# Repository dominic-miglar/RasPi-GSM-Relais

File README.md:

# RasPi-GSM-Relais

## Folder structure

#### data_sheets

contains the data sheets of the components

#### eagle

contains the eagle files

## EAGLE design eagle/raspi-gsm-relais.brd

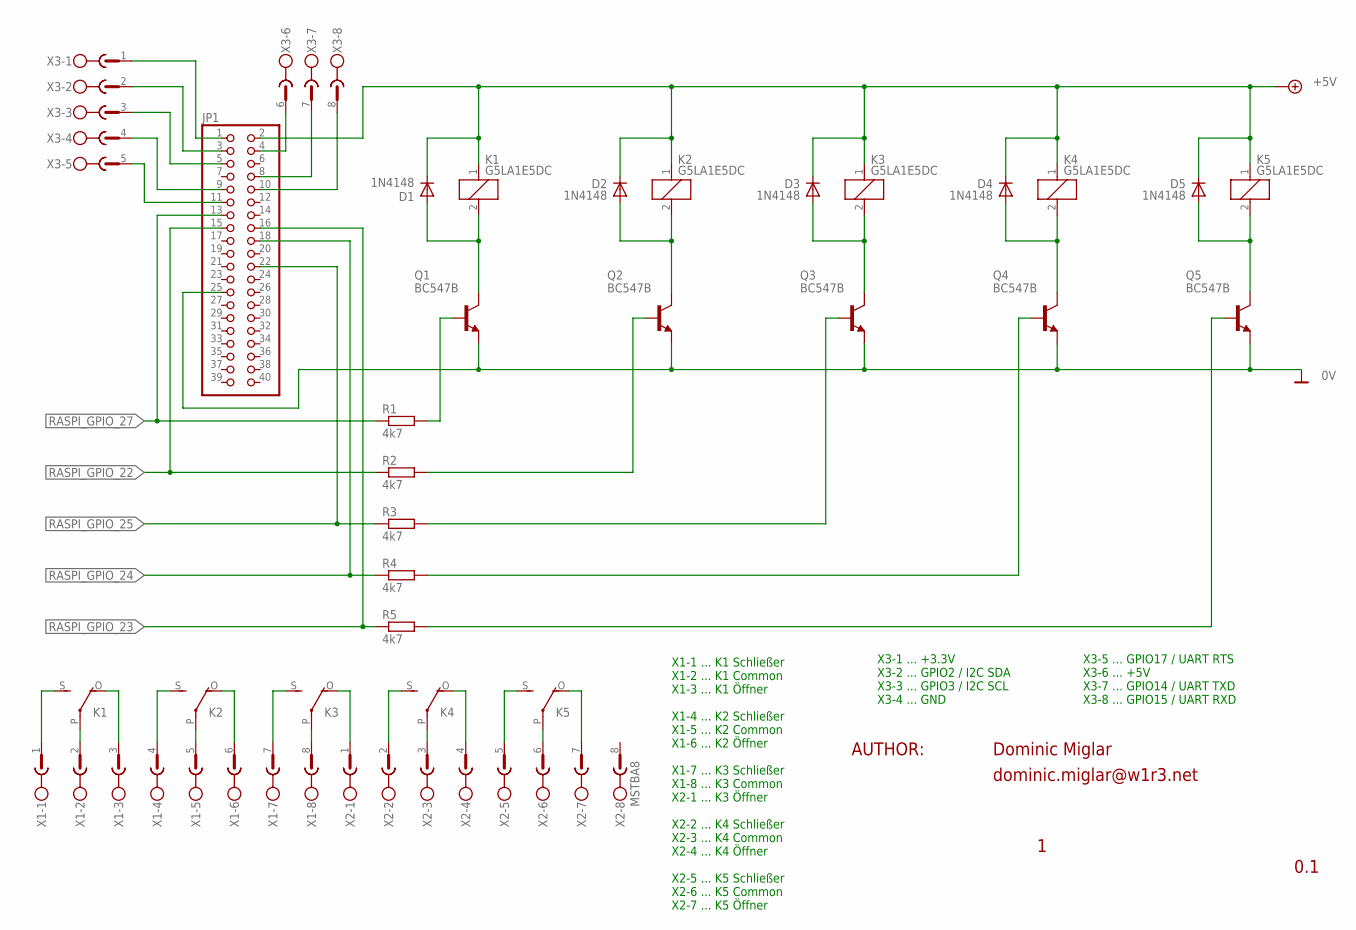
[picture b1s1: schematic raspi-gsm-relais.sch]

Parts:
D1, D2, D3, D4, D5: 1N4148; DO35-10
JP1: PINHD-2X20; 2X20
K1, K2, K3, K4, K5: G5LA1E5DC; G5LE
Q1, Q2, Q3, Q4, Q5: BC547B; TO92
R1, R2, R3, R4, R5: 4k7; 0207/10
X1, X2, X3: MSTBA8

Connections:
0V: JP1.25, Q1.1 (E), Q2.1 (E), Q3.1 (E), Q4.1 (E), Q5.1 (E)
+5V: D1.C, D2.C, D3.C, D4.C, D5.C, JP1.2, K1.1, K2.1, K3.1, K4.1, K5.1
unnamed: D1.A, K1.2, Q1.3 (C)
unnamed: D2.A, K2.2, Q2.3 (C)
unnamed: D3.A, K3.2, Q3.3 (C)
unnamed: D4.A, K4.2, Q4.3 (C)
unnamed: D5.A, K5.2, Q5.3 (C)
unnamed: JP1.1, X3.1
unnamed: Q2.2 (B), R2.2
unnamed: Q3.2 (B), R3.2
unnamed: Q4.2 (B), R4.2
unnamed: Q5.2 (B), R5.2
unnamed: K4.P, X2.3
unnamed: K1.P, X1.2
unnamed: K1.O, X1.3
unnamed: K1.S, X1.1
unnamed: K2.P, X1.5
unnamed: K2.O, X1.6
unnamed: K2.S, X1.4
unnamed: K3.P, X1.8
unnamed: K3.O, X2.1
unnamed: K3.S, X1.7
unnamed: K4.O, X2.4
unnamed: K4.S, X2.2
unnamed: K5.P, X2.6
unnamed: K5.S, X2.5
unnamed: K5.O, X2.7
unnamed: Q1.2 (B), R1.2
unnamed: JP1.3, X3.2
unnamed: JP1.5, X3.3
unnamed: JP1.9, X3.4
unnamed: JP1.11, X3.5
unnamed: JP1.4, X3.6
unnamed: JP1.8, X3.7
unnamed: JP1.10, X3.8
RASPI_GPIO_22: JP1.15, R2.1
RASPI_GPIO_23: JP1.16, R5.1
RASPI_GPIO_24: JP1.18, R4.1
RASPI_GPIO_25: JP1.22, R3.1
RASPI_GPIO_27: JP1.13, R1.1

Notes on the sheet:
X1-1 ... K1 Schließer X1-2 ... K1 Common X1-3 ... K1 Öffner X1-4 ... K2 Schließer X1-5 ... K2 Common X1-6 ... K2 Öffner X1-7 ... K3 Schließer X1-8 ... K3 Common X2-1 ... K3 Öffner X2-2 ... K4 Schließer X2-3 ... K4 Common X2-4 ... K4 Öffner X2-5 ... K5 Schließer X2-6 ... K5 Common X2-7 ... K5 Öffner
X3-1 ... +3.3V X3-2 ... GPIO2 / I2C SDA X3-3 ... GPIO3 / I2C SCL X3-4 ... GND
X3-5 ... GPIO17 / UART RTS X3-6 ... +5V X3-7 ... GPIO14 / UART TXD X3-8 ... GPIO15 / UART RXD
AUTHOR:
dominic.miglar@w1r3.net
Dominic Miglar
0.1

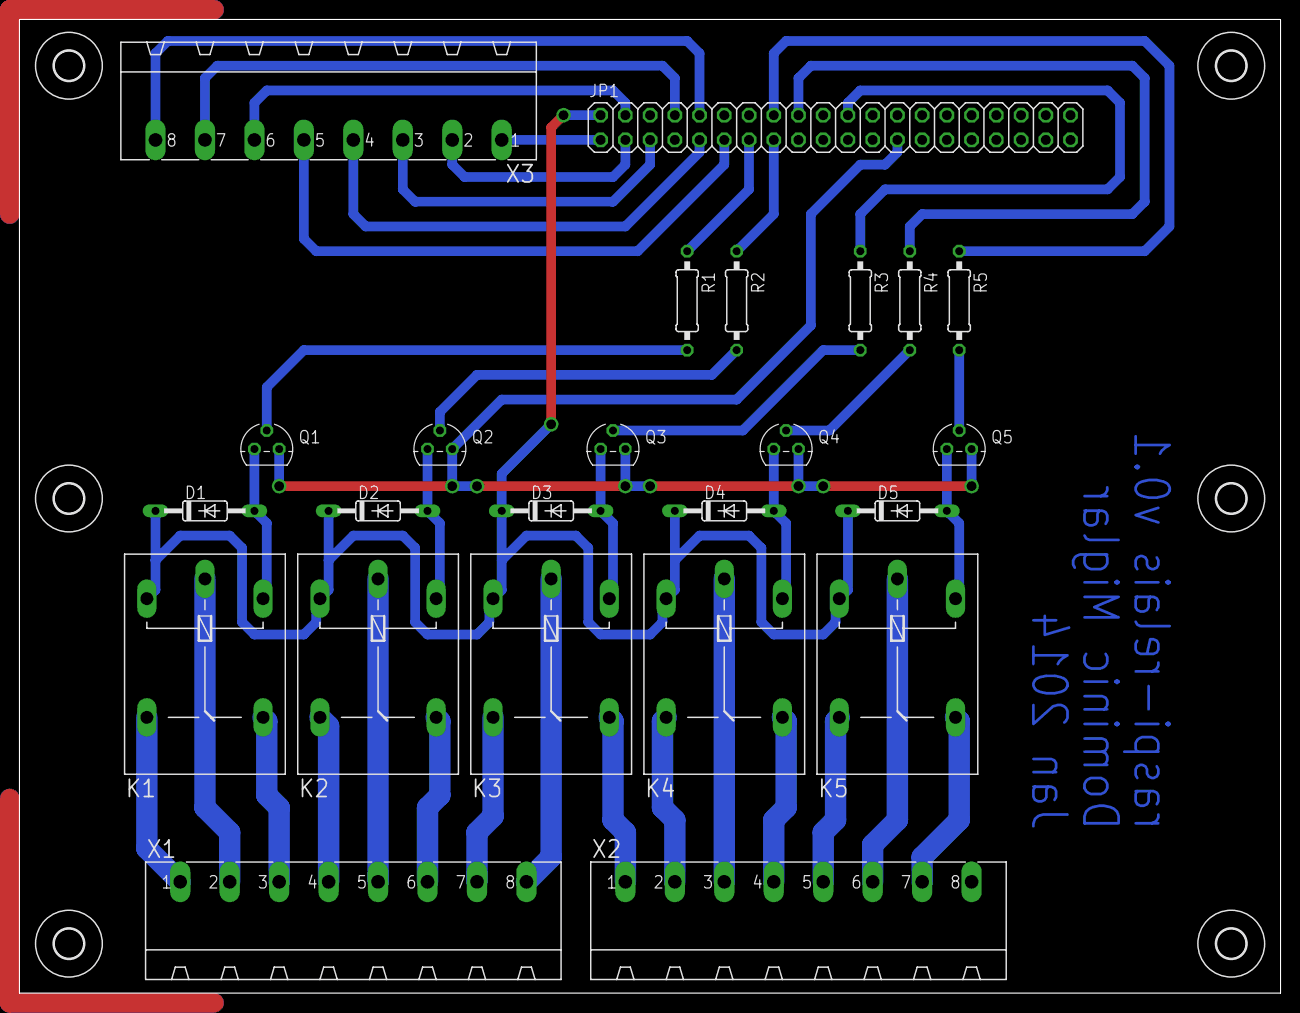
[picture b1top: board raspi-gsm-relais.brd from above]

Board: 2 copper layers, 129.5 x 100.0 mm, 30 parts (0 on the bottom side), 40 nets.

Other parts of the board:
U$1, U$2, U$3, U$4, U$5, U$6: 3,0

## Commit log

2013-11-29 changed README.md
2013-12-03 added data sheets
2013-12-06 pdf aktualisiert
2013-12-06 schaltplan geaendert
2014-01-04 eagle files modified :)
2014-01-05 fertig #1
2014-01-05 renamed files
2014-01-05 added DESCRIPTION
2014-01-06 asdf
2014-01-06 fertig
